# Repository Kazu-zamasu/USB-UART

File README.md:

# USB-UART
Build on KiCAD EDA
作ってみましたが、無保証で。
いかに現在販売されてるのが良い出来で安いのか判る為に作った。
このタイプは二重絶縁。普通は必要ないです。一重絶縁で十分。売ってるもの買ったほうが安いです。

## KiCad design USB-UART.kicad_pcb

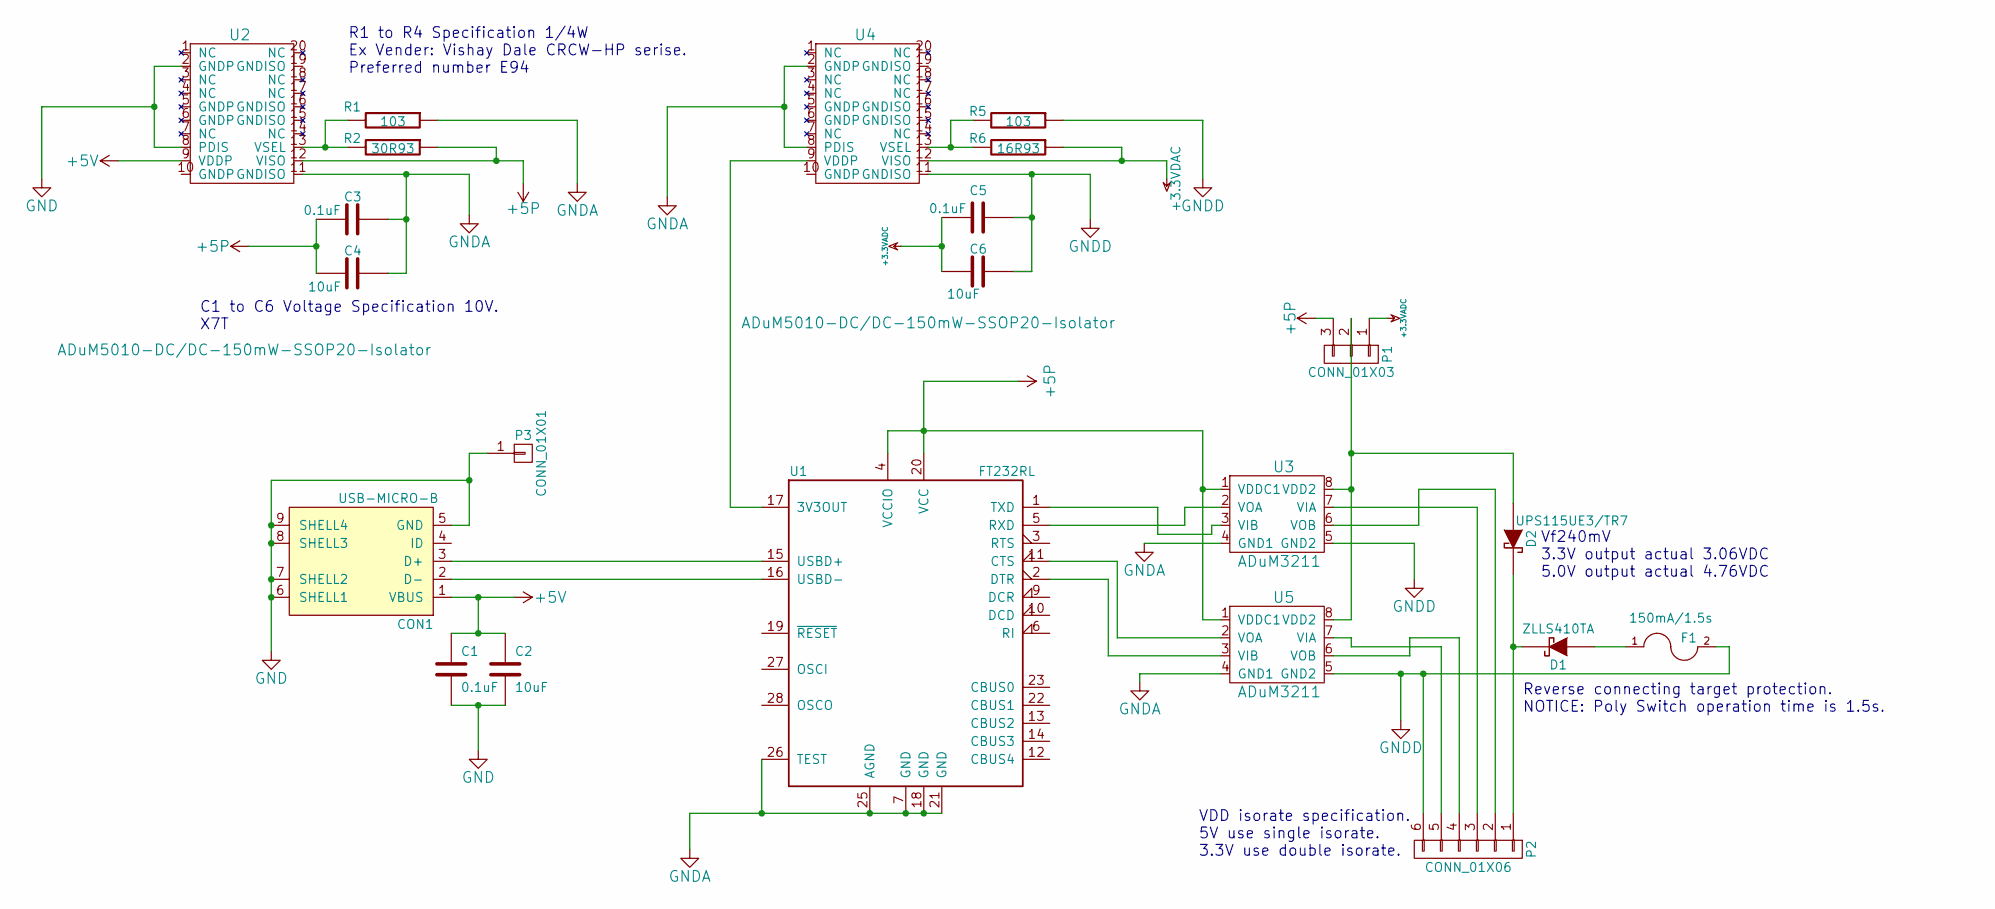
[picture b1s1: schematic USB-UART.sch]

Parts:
C1, C3, C5: 0.1uF; SMD-0603_c
C2, C4, C6: 10uF; SMD-0603_c
CON1: USB-MICRO-B; Hirose-microUSB-ZX62R-B-5P
D1: ZLLS410TA; ZLLS410
D2: UPS115UE3/TR7; UPS115UE3_TR7
F1: 150mA/1.5s; SMD-1210
P1: CONN_01X03
P2: CONN_01X06; Socket_Strip_Angled_1x06
P3: CONN_01X01; EarthPad
R1, R5: 103; SMD-0603_r
R2: 30R93; SMD-0603_r
R6: 16R93; SMD-0603_r
U1: FT232RL; SSOP-28_5.3x10.2mm_Pitch0.65mm
U2, U4: ADuM5010-DC/DC-150mW-SSOP20-Isolator; SSOP-20_5.3x7.2mm_Pitch0.65mm
U3, U5: ADuM3211; SOIC-8_3.9x4.9mm_Pitch1.27mm

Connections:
+3.3VADC: C5.2, C6.2, P1.1
+3.3VDAC: R6.1, U4.12 (VISO)
+5P: C3.2, C4.2, P1.3, R2.1, U1.4 (VCCIO), U1.20 (VCC), U2.12 (VISO), U3.1 (VDDC1), U5.1 (VDDC1)
+5V: C1.1, C2.1, CON1.1 (VBUS), U2.9 (VDDP)
GND: C1.2, C2.2, CON1.5 (GND), CON1.6 (SHELL1), CON1.7 (SHELL2), CON1.8 (SHELL3), CON1.9 (SHELL4), P3.1, U2.2 (GNDP), U2.8 (PDIS)
GNDA: C3.1, C4.1, R1.1, U1.7 (GND), U1.18 (GND), U1.21 (GND), U1.25 (AGND), U1.26 (TEST), U2.11 (GNDISO), U3.4 (GND1), U4.2 (GNDP), U4.8 (PDIS), U5.4 (GND1)
GNDD: C5.1, C6.1, F1.2, P2.6, R5.1, U3.5 (GND2), U4.11 (GNDISO), U5.5 (GND2)
unnamed: CON1.2 (D-), U1.16 (USBD-)
unnamed: CON1.3 (D+), U1.15 (USBD+)
unnamed: D1.1 (A), F1.1
unnamed: D1.2 (K), D2.2 (K), P2.1
unnamed: D2.1 (A), P1.2, U3.8 (VDD2), U5.8 (VDD2)
unnamed: P2.2, U3.6 (VOB)
unnamed: P2.3, U3.7 (VIA)
unnamed: P2.4, U5.6 (VOB)
unnamed: P2.5, U5.7 (VIA)
unnamed: R1.2, R2.2, U2.13 (VSEL)
unnamed: R5.2, R6.2, U4.13 (VSEL)
unnamed: U1.1 (TXD), U3.3 (VIB)
unnamed: U1.2 (DTR), U5.3 (VIB)
unnamed: U1.5 (RXD), U3.2 (VOA)
unnamed: U1.11 (CTS), U5.2 (VOA)
unnamed: U1.17 (3V3OUT), U4.9 (VDDP)

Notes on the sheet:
Vf240mV 3.3V output actual 3.06VDC 5.0V output actual 4.76VDC
VDD isorate specification. 5V use single isorate. 3.3V use double isorate.
C1 to C6 Voltage Specification 10V. X7T
R1 to R4 Specification 1/4W Ex Vender: Vishay Dale CRCW-HP serise. Preferred number E94
Reverse connecting target protection. NOTICE: Poly Switch operation time is 1.5s.

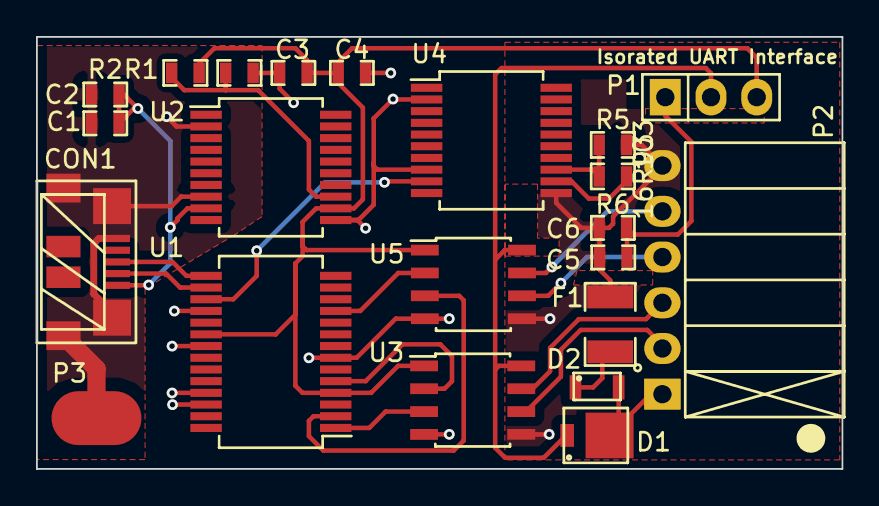
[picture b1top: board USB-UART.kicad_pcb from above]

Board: 2 copper layers, 44.8 x 24.0 mm, 22 parts (0 on the bottom side), 23 nets.

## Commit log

2015-03-19 First commmit
    Free USE no guarantee
2015-03-19 Dress to ground.
2015-03-19 Change to wire
